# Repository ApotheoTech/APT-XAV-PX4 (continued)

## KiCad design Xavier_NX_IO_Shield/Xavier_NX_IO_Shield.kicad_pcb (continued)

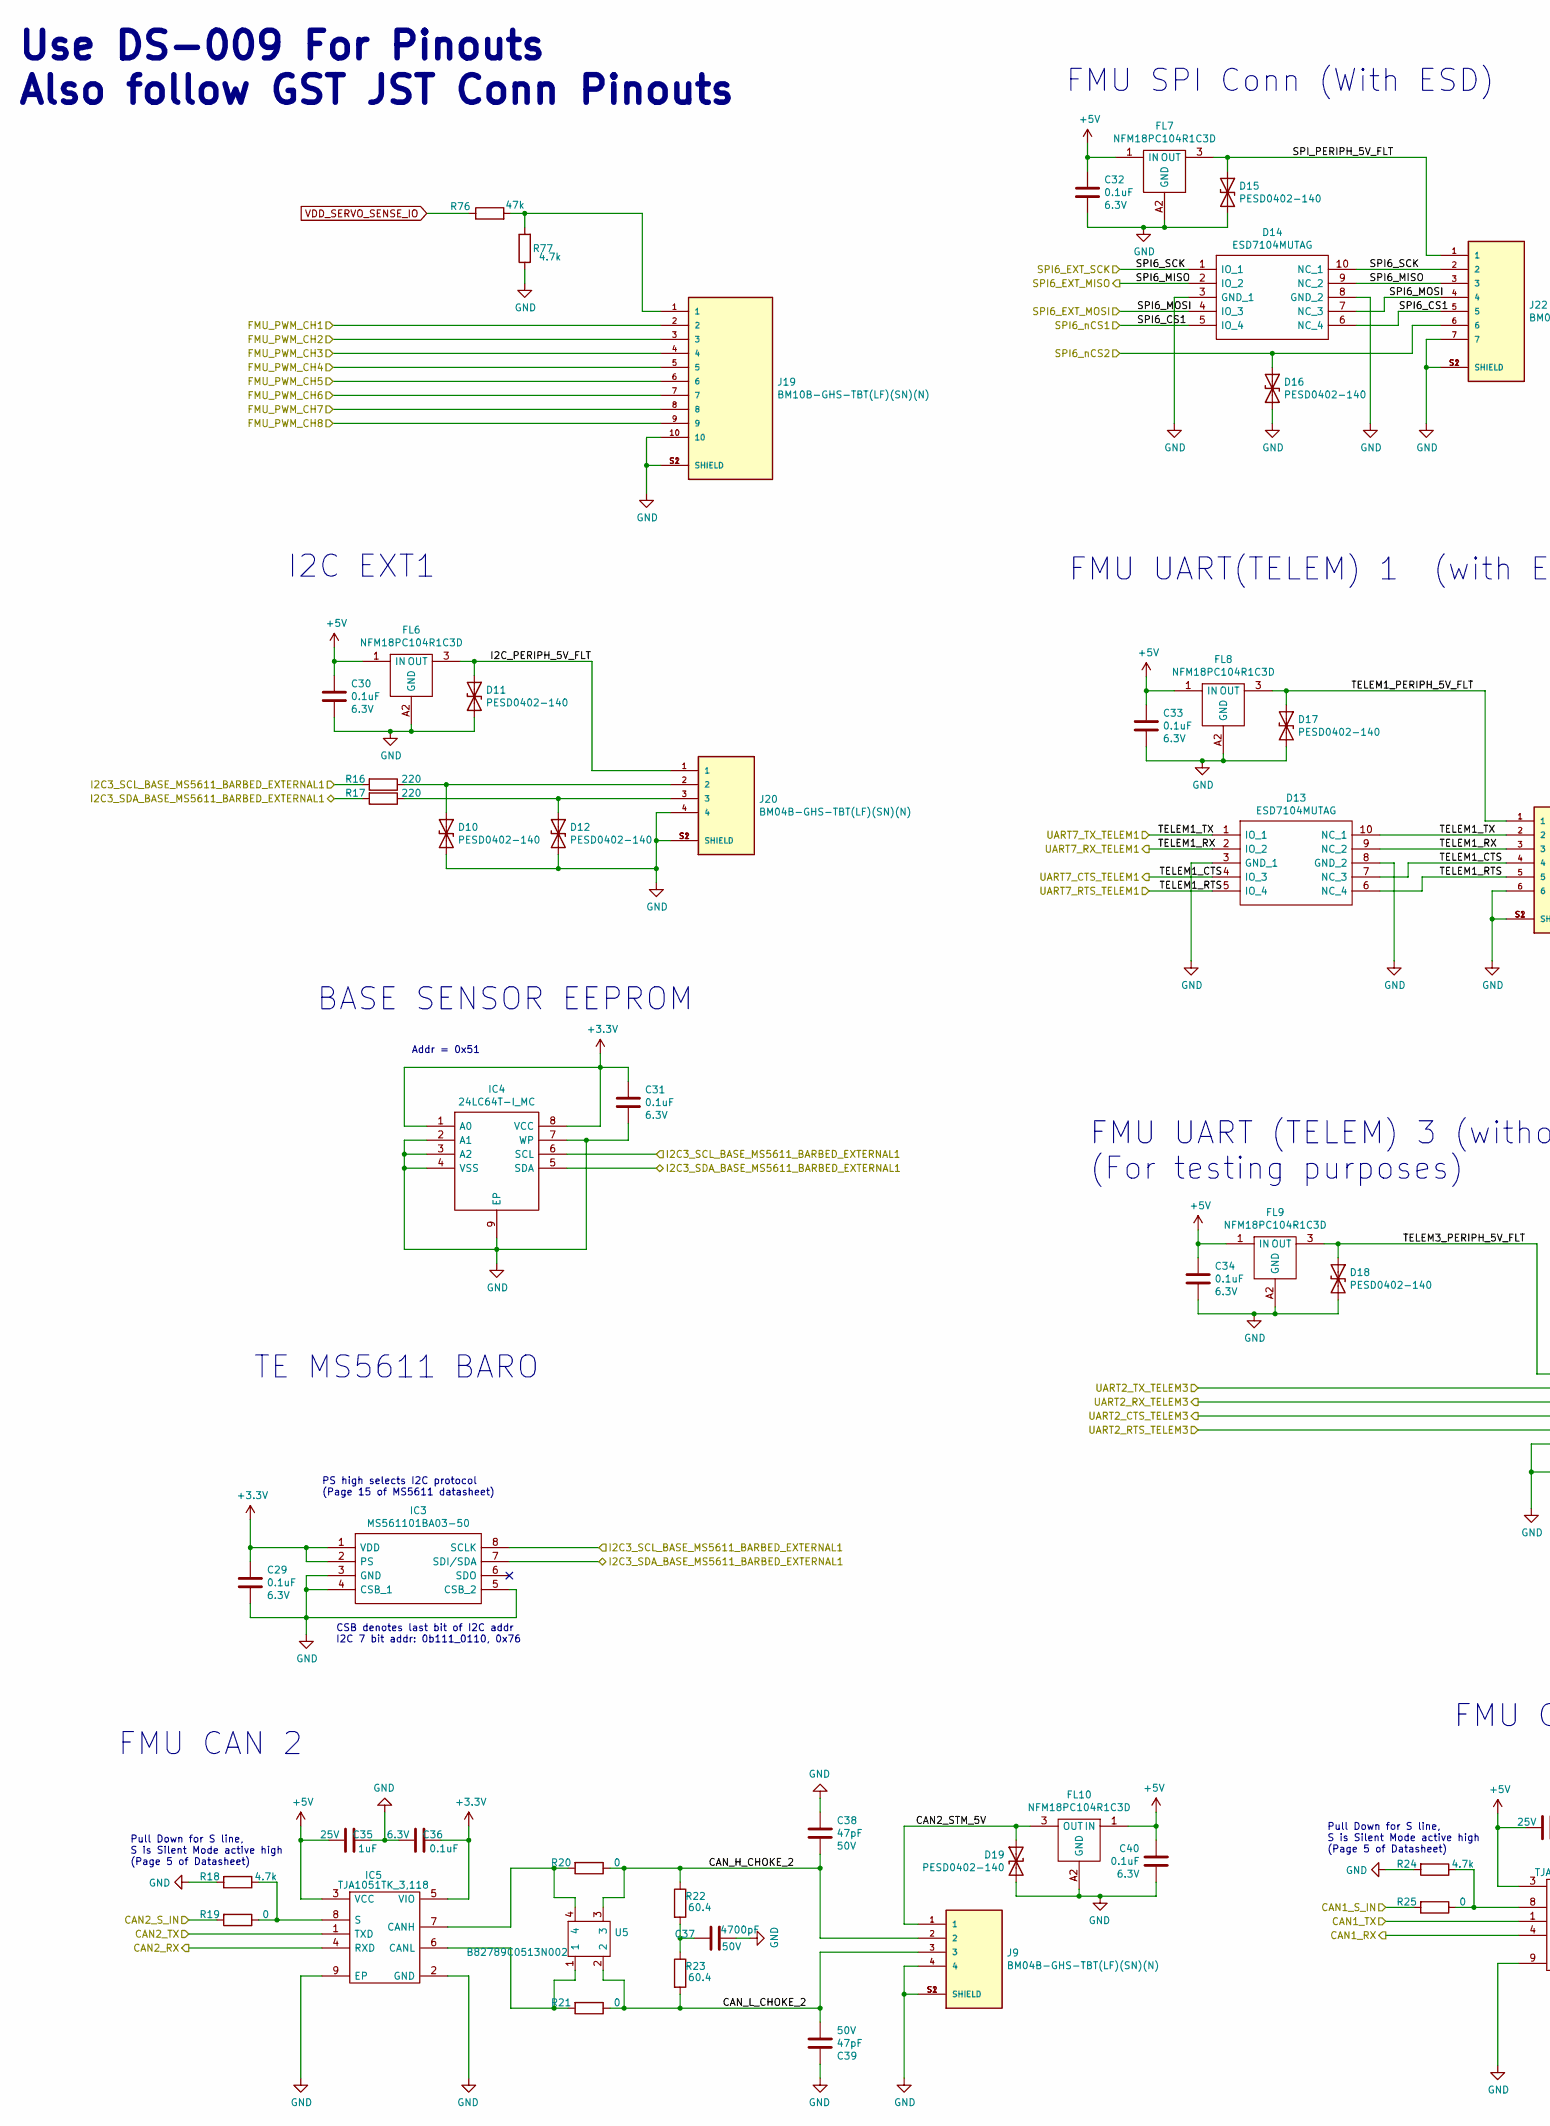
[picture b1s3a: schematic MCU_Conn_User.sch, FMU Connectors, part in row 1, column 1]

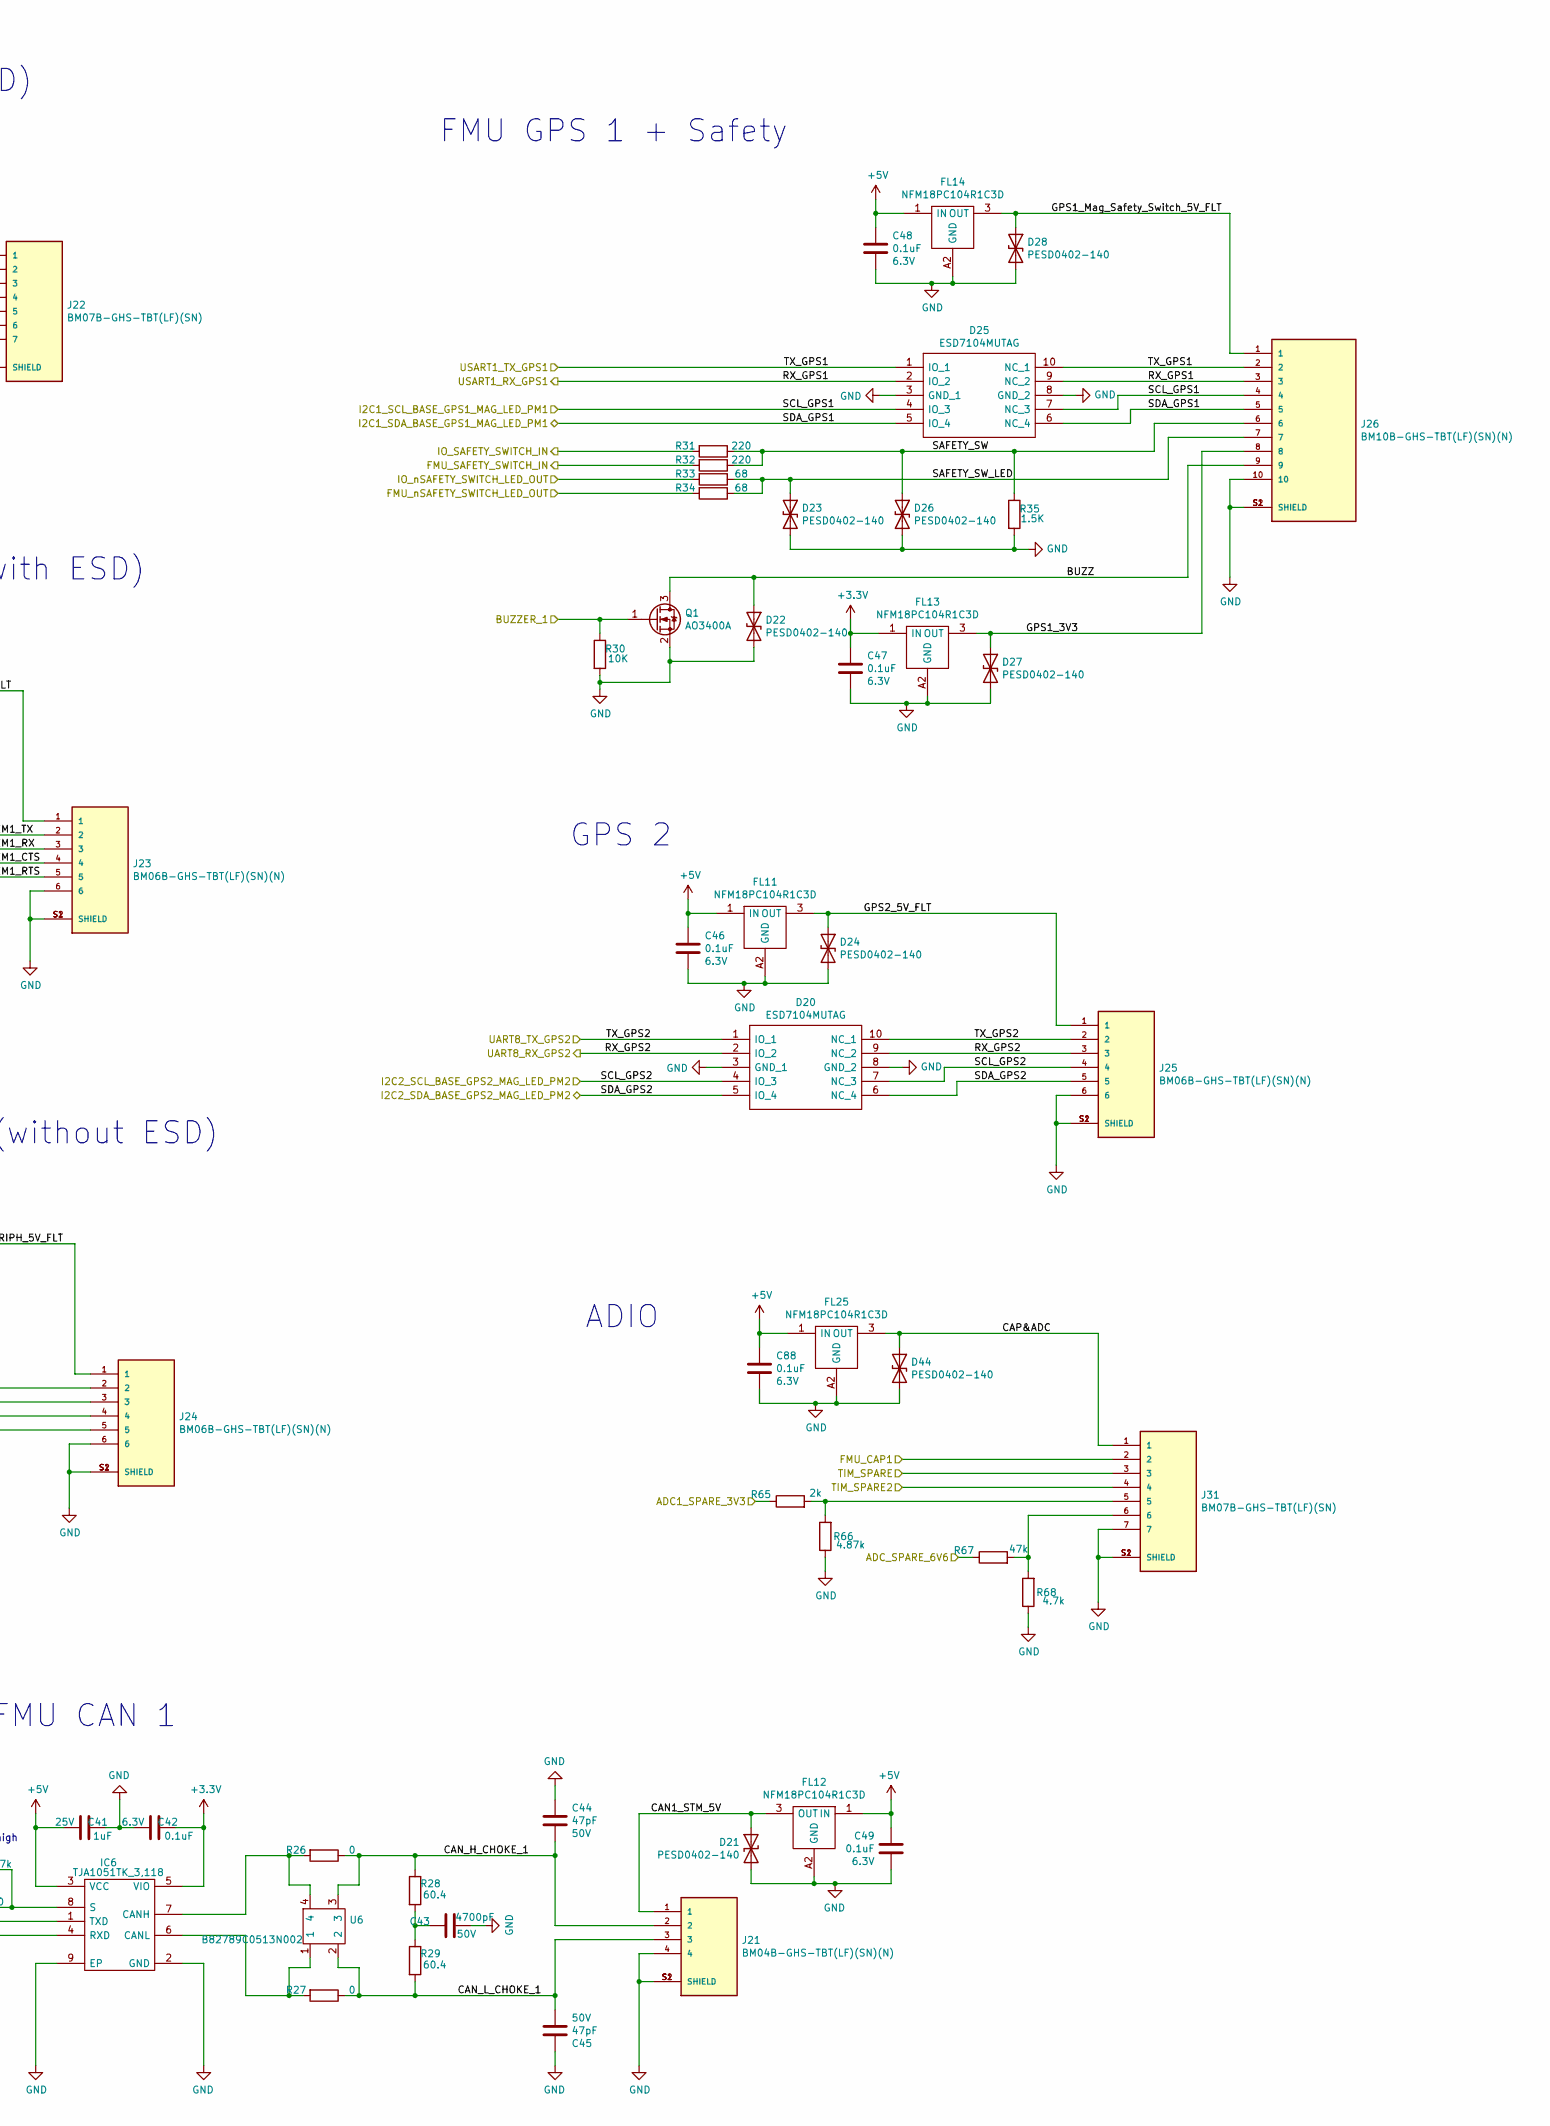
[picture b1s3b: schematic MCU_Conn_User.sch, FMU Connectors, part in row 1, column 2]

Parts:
C29, C30, C31, C32, C33, C34, C36, C40, C42, C46, C47, C48, C49, C88: 0.1uF; C_0402_1005Metric; Voltage 6.3V; PartNumber C1005X5R0J104K050BA
C35, C41: 1uF; C_0402_1005Metric; Voltage 25V; PartNumber GRT155R61E105KE01D
C37, C43: 4700pF; C_0402_1005Metric; Voltage 50V; PartNumber 0402B472J500CT
C38, C39, C44, C45: 47pF; C_0402_1005Metric; Voltage 50V; PartNumber C0402C470J5GACTU
D10, D11, D12, D15, D16, D17, D18, D19, D21, D22, D23, D24, D26, D27, D28, D44: PESD0402-140; PESD0402
D13, D14, D20, D25: ESD7104MUTAG; ESD8104MUTAG; Mouser Part Number 863-ESD7104MUTAG
FL6, FL7, FL8, FL9, FL10, FL11, FL12, FL13, FL14, FL25: NFM18PC104R1C3D; Manufacturer_Part_Number NFM18PC104R1C3D
IC3: MS561101BA03-50; Mouser Part Number 824-MS561101BA03-50
IC4: 24LC64T-I_MC; 24LC64T; Mouser Part Number 579-24LC64T-I/MC
IC5, IC6: TJA1051TK_3,118; TJA1051TK3; Mouser Part Number 771-TJA1051TK/3118
J9, J20, J21: BM04B-GHS-TBT(LF)(SN)(N); PARTREV N/A
J19, J26: BM10B-GHS-TBT(LF)(SN)(N); PARTREV N/A
J22, J31: BM07B-GHS-TBT(LF)(SN); PARTREV NA
J23, J24, J25: BM06B-GHS-TBT(LF)(SN)(N); PARTREV N/A
Q1: AO3400A; SOT-23
R16, R17, R31, R32: 220; R_0402_1005Metric; PartNumber RC0402JR-07220RL
R18, R24: 4.7k; R_0402_1005Metric; PartNumber RC0402FR-074K7L
R19, R20, R21, R25, R26, R27: 0; R_0402_1005Metric; PartNumber CRCW04020000Z0EDHP
R22, R23, R28, R29: 60.4; R_0402_1005Metric; PartNumber ERJ-2RKF60R4X‎
R30: 10K; R_0402_1005Metric; PartNumber ERJ-2RKF1002X
R33, R34: 68; R_0402_1005Metric; PartNumber ‎ERJ-2RKF68R0X‎
R35: 1.5K; R_0402_1005Metric; PartNumber ERJ-2RKF1501X
R65: 2k; R_0402_1005Metric; PartNumber CRCW04022K00FKED
R66: 4.87k; R_0402_1005Metric; PartNumber ERJ-2RKF4871X
R67, R76: 47k; R_0402_1005Metric; PartNumber RCC040247K0FKED
R68, R77: 4.7k; R_0402_1005Metric; PartNumber RCC04024K70FKED
U5, U6: B82789C0513N002; B82789C0113N002

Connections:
+3V3: C29.1, C31.1, C36.2, C42.2, C47.1, FL13.1 (IN), IC3.1 (VDD), IC3.2 (PS), IC4.1 (A0), IC4.8 (VCC), IC5.5 (VIO), IC6.5 (VIO); also elsewhere on the board
+5V: C30.1, C32.1, C33.1, C34.1, C35.1, C40.1, C41.1, C46.1, C48.1, C49.1, C88.1, FL6.1 (IN), FL7.1 (IN), FL8.1 (IN), FL9.1 (IN), FL10.1 (IN), FL11.1 (IN), FL12.1 (IN), FL14.1 (IN), FL25.1 (IN), IC5.3 (VCC), IC6.3 (VCC); also elsewhere on the board
/ADC3_3V3: R65.1; also elsewhere on the board
/ADC3_6V6: R67.1; also elsewhere on the board
/BUZZER1: Q1.1 (G), R30.1; also elsewhere on the board
/CAN1_RX: IC6.4 (RXD); also elsewhere on the board
/CAN1_TX: IC6.1 (TXD); also elsewhere on the board
/CAN2_RX: IC5.4 (RXD); also elsewhere on the board
/CAN2_TX: IC5.1 (TXD); also elsewhere on the board
/FMU_CAP1: J31.2; also elsewhere on the board
/FMU_CH1: J19.2; also elsewhere on the board
/FMU_CH2: J19.3; also elsewhere on the board
/FMU_CH3: J19.4; also elsewhere on the board
/FMU_CH4: J19.5; also elsewhere on the board
/FMU_CH5: J19.6; also elsewhere on the board
/FMU_CH6: J19.7; also elsewhere on the board
/FMU_CH7: J19.8; also elsewhere on the board
/FMU_CH8: J19.9; also elsewhere on the board
/FMU_SAFETY_SWITCH_IN: R32.2; also elsewhere on the board
/FMU_nSAFETY_SWITCH_LED_OUT: R34.2; also elsewhere on the board
/I2C1_SCL_BASE_GPS1_MAG_LED_PM1: D25.4 (IO_3), D25.7 (NC_3), J26.4; also elsewhere on the board
/I2C1_SDA_BASE_GPS1_MAG_LED_PM1: D25.5 (IO_4), D25.6 (NC_4), J26.5; also elsewhere on the board
/I2C2_SCL_BASE_GPS2_MAG_LED_PM2: D20.4 (IO_3), D20.7 (NC_3), J25.4; also elsewhere on the board
/I2C2_SDA_BASE_GPS2_MAG_LED_PM2: D20.5 (IO_4), D20.6 (NC_4), J25.5; also elsewhere on the board
/I2C3_SCL_BASE_MS5611_BARBED_EXTERNAL: IC3.8 (SCLK), IC4.6 (SCL), R16.2; also elsewhere on the board
/I2C3_SDA_BASE_MS5611_BARBED_EXTERNAL: IC3.7 (SDI/SDA), IC4.5 (SDA), R17.2; also elsewhere on the board
/IO_SAFETY_SWITCH_IN: R31.2; also elsewhere on the board
/IO_nSAFETY_SWITCH_LED_OUT: R33.2; also elsewhere on the board
/MCU_Conn_User/BUZZ: D22.1 (A1), J26.9, Q1.3 (D)
/MCU_Conn_User/CAN1_STM_5V: D21.1 (A1), FL12.3 (OUT), J21.1
/MCU_Conn_User/CAN2_STM_5V: D19.1 (A1), FL10.3 (OUT), J9.1
/MCU_Conn_User/CAN_H_CHOKE_1: C44.2, J21.2, R26.1, R28.1, U6.3
/MCU_Conn_User/CAN_H_CHOKE_2: C38.2, J9.2, R20.1, R22.1, U5.3
/MCU_Conn_User/CAN_L_CHOKE_1: C45.2, J21.3, R27.1, R29.2, U6.2
/MCU_Conn_User/CAN_L_CHOKE_2: C39.2, J9.3, R21.1, R23.2, U5.2
/MCU_Conn_User/CAP&ADC: D44.1 (A1), FL25.3 (OUT), J31.1
/MCU_Conn_User/GPS1_3V3: D27.1 (A1), FL13.3 (OUT), J26.8
/MCU_Conn_User/GPS1_Mag_Safety_Switch_5V_FLT: D28.1 (A1), FL14.3 (OUT), J26.1
/MCU_Conn_User/GPS2_5V_FLT: D24.1 (A1), FL11.3 (OUT), J25.1
/MCU_Conn_User/I2C_PERIPH_5V_FLT: D11.1 (A1), FL6.3 (OUT), J20.1
/MCU_Conn_User/SAFETY_SW: D26.1 (A1), J26.6, R31.1, R32.1, R35.1
/MCU_Conn_User/SAFETY_SW_LED: D23.1 (A1), J26.7, R33.1, R34.1
/MCU_Conn_User/SPI_PERIPH_5V_FLT: D15.1 (A1), FL7.3 (OUT), J22.1
/MCU_Conn_User/TELEM1_PERIPH_5V_FLT: D17.1 (A1), FL8.3 (OUT), J23.1
/MCU_Conn_User/TELEM3_PERIPH_5V_FLT: D18.1 (A1), FL9.3 (OUT), J24.1
/SPI6_DRDY2_EXTERNAL1: J31.3; also elsewhere on the board
/SPI6_MISO_EXTERNAL1: D14.2 (IO_2), D14.9 (NC_2), J22.3; also elsewhere on the board
/SPI6_MOSI_EXTERNAL1: D14.4 (IO_3), D14.7 (NC_3), J22.4; also elsewhere on the board
/SPI6_SCK_EXTERAL1: D14.1 (IO_1), D14.10 (NC_1), J22.2; also elsewhere on the board
/SPI6_nCS1_EXTERNAL1: D14.5 (IO_4), D14.6 (NC_4), J22.5; also elsewhere on the board
/SPI6_nCS2_EXTERNAL1: D16.1 (A1), J22.6; also elsewhere on the board
/SPIX_SYNC: J31.4; also elsewhere on the board
/UART7_CTS_TELEM1: D13.4 (IO_3), D13.7 (NC_3), J23.4; also elsewhere on the board
/UART7_RTS_TELEM1: D13.5 (IO_4), D13.6 (NC_4), J23.5; also elsewhere on the board
/UART7_RX_TELEM1: D13.2 (IO_2), D13.9 (NC_2), J23.3; also elsewhere on the board
/UART7_TX_TELEM1: D13.1 (IO_1), D13.10 (NC_1), J23.2; also elsewhere on the board
/UART8_RX_GPS2: D20.2 (IO_2), D20.9 (NC_2), J25.3; also elsewhere on the board
/UART8_TX_GPS2: D20.1 (IO_1), D20.10 (NC_1), J25.2; also elsewhere on the board
/USART1_RX_GPS1: D25.2 (IO_2), D25.9 (NC_2), J26.3; also elsewhere on the board
/USART1_TX_GPS1: D25.1 (IO_1), D25.10 (NC_1), J26.2; also elsewhere on the board
/USART2_CTS_TELEM3: J24.4; also elsewhere on the board
/USART2_RTS_TELEM3: J24.5; also elsewhere on the board
/USART2_RX_TELEM3: J24.3; also elsewhere on the board
/USART2_TX_TELEM3: J24.2; also elsewhere on the board
/nPOWER_IN_B: R19.2; also elsewhere on the board
/nPOWER_IN_C: R25.2; also elsewhere on the board
GND: C29.2, C30.2, C31.2, C32.2, C33.2, C34.2, C35.2, C36.1, C37.2, C38.1, C39.1, C40.2, C41.2, C42.1, C43.2, C44.1, C45.1, C46.2, C47.2, C48.2, C49.2, C88.2, D10.2 (A2), D11.2 (A2), D12.2 (A2), D13.3 (GND_1), D13.8 (GND_2), D14.3 (GND_1), D14.8 (GND_2), D15.2 (A2), D16.2 (A2), D17.2 (A2), D18.2 (A2), D19.2 (A2), D20.3 (GND_1), D20.8 (GND_2), D21.2 (A2), D22.2 (A2), D23.2 (A2), D24.2 (A2), D25.3 (GND_1), D25.8 (GND_2), D26.2 (A2), D27.2 (A2), D28.2 (A2), D44.2 (A2), FL6.A2 (GND), FL7.A2 (GND), FL8.A2 (GND), FL9.A2 (GND), FL10.A2 (GND), FL11.A2 (GND), FL12.A2 (GND), FL13.A2 (GND), FL14.A2 (GND), FL25.A2 (GND), IC3.3 (GND), IC3.4 (CSB_1), IC3.5 (CSB_2), IC4.2 (A1), IC4.3 (A2), IC4.4 (VSS), IC4.7 (WP), IC4.9 (EP), IC5.2 (GND), IC5.9 (EP), IC6.2 (GND), IC6.9 (EP), J9.4, J9.S1 (SHIELD), J9.S2 (SHIELD), J19.10, J19.S1 (SHIELD), J19.S2 (SHIELD), J20.4, J20.S1 (SHIELD), J20.S2 (SHIELD), J21.4, J21.S1 (SHIELD), J21.S2 (SHIELD), J22.7, J22.S1 (SHIELD), J22.S2 (SHIELD), J23.6, J23.S1 (SHIELD), J23.S2 (SHIELD), J24.6, J24.S1 (SHIELD), J24.S2 (SHIELD), J25.6, J25.S1 (SHIELD), J25.S2 (SHIELD), J26.10, J26.S1 (SHIELD), J26.S2 (SHIELD), J31.7, J31.S1 (SHIELD), J31.S2 (SHIELD), Q1.2 (S), R18.2, R24.2, R30.2, R35.2, R66.1, R68.1, R77.1; also elsewhere on the board
unnamed: C37.1, R22.2, R23.1
unnamed: C43.1, R28.2, R29.1
unnamed: D10.1 (A1), J20.2, R16.1
unnamed: D12.1 (A1), J20.3, R17.1
unnamed: IC5.6 (CANL), R21.2, U5.1
unnamed: IC5.7 (CANH), R20.2, U5.4
unnamed: IC5.8 (S), R18.1, R19.1
unnamed: IC6.6 (CANL), R27.2, U6.1
unnamed: IC6.7 (CANH), R26.2, U6.4
unnamed: IC6.8 (S), R24.1, R25.1
unnamed: J19.1, R76.2, R77.2
unnamed: J31.5, R65.2, R66.2
unnamed: J31.6, R67.2, R68.2
VDD_SERVO_SENSE_IO: R76.1; also elsewhere on the board

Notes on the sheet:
I2C EXT1
BASE SENSOR EEPROM
Addr = 0x51
TE MS5611 BARO
FMU SPI Conn (With ESD)
FMU UART(TELEM) 1 (with ESD)
FMU UART (TELEM) 3 (without ESD) (For testing purposes)
FMU CAN 1
FMU CAN 2
FMU GPS 1 + Safety
GPS 2
ADIO
CSB denotes last bit of I2C addr I2C 7 bit addr: 0b111_0110, 0x76
PS high selects I2C protocol (Page 15 of MS5611 datasheet)
Use DS-009 For Pinouts Also follow GST JST Conn Pinouts
Pull Down for S line, S is Silent Mode active high (Page 5 of Datasheet)

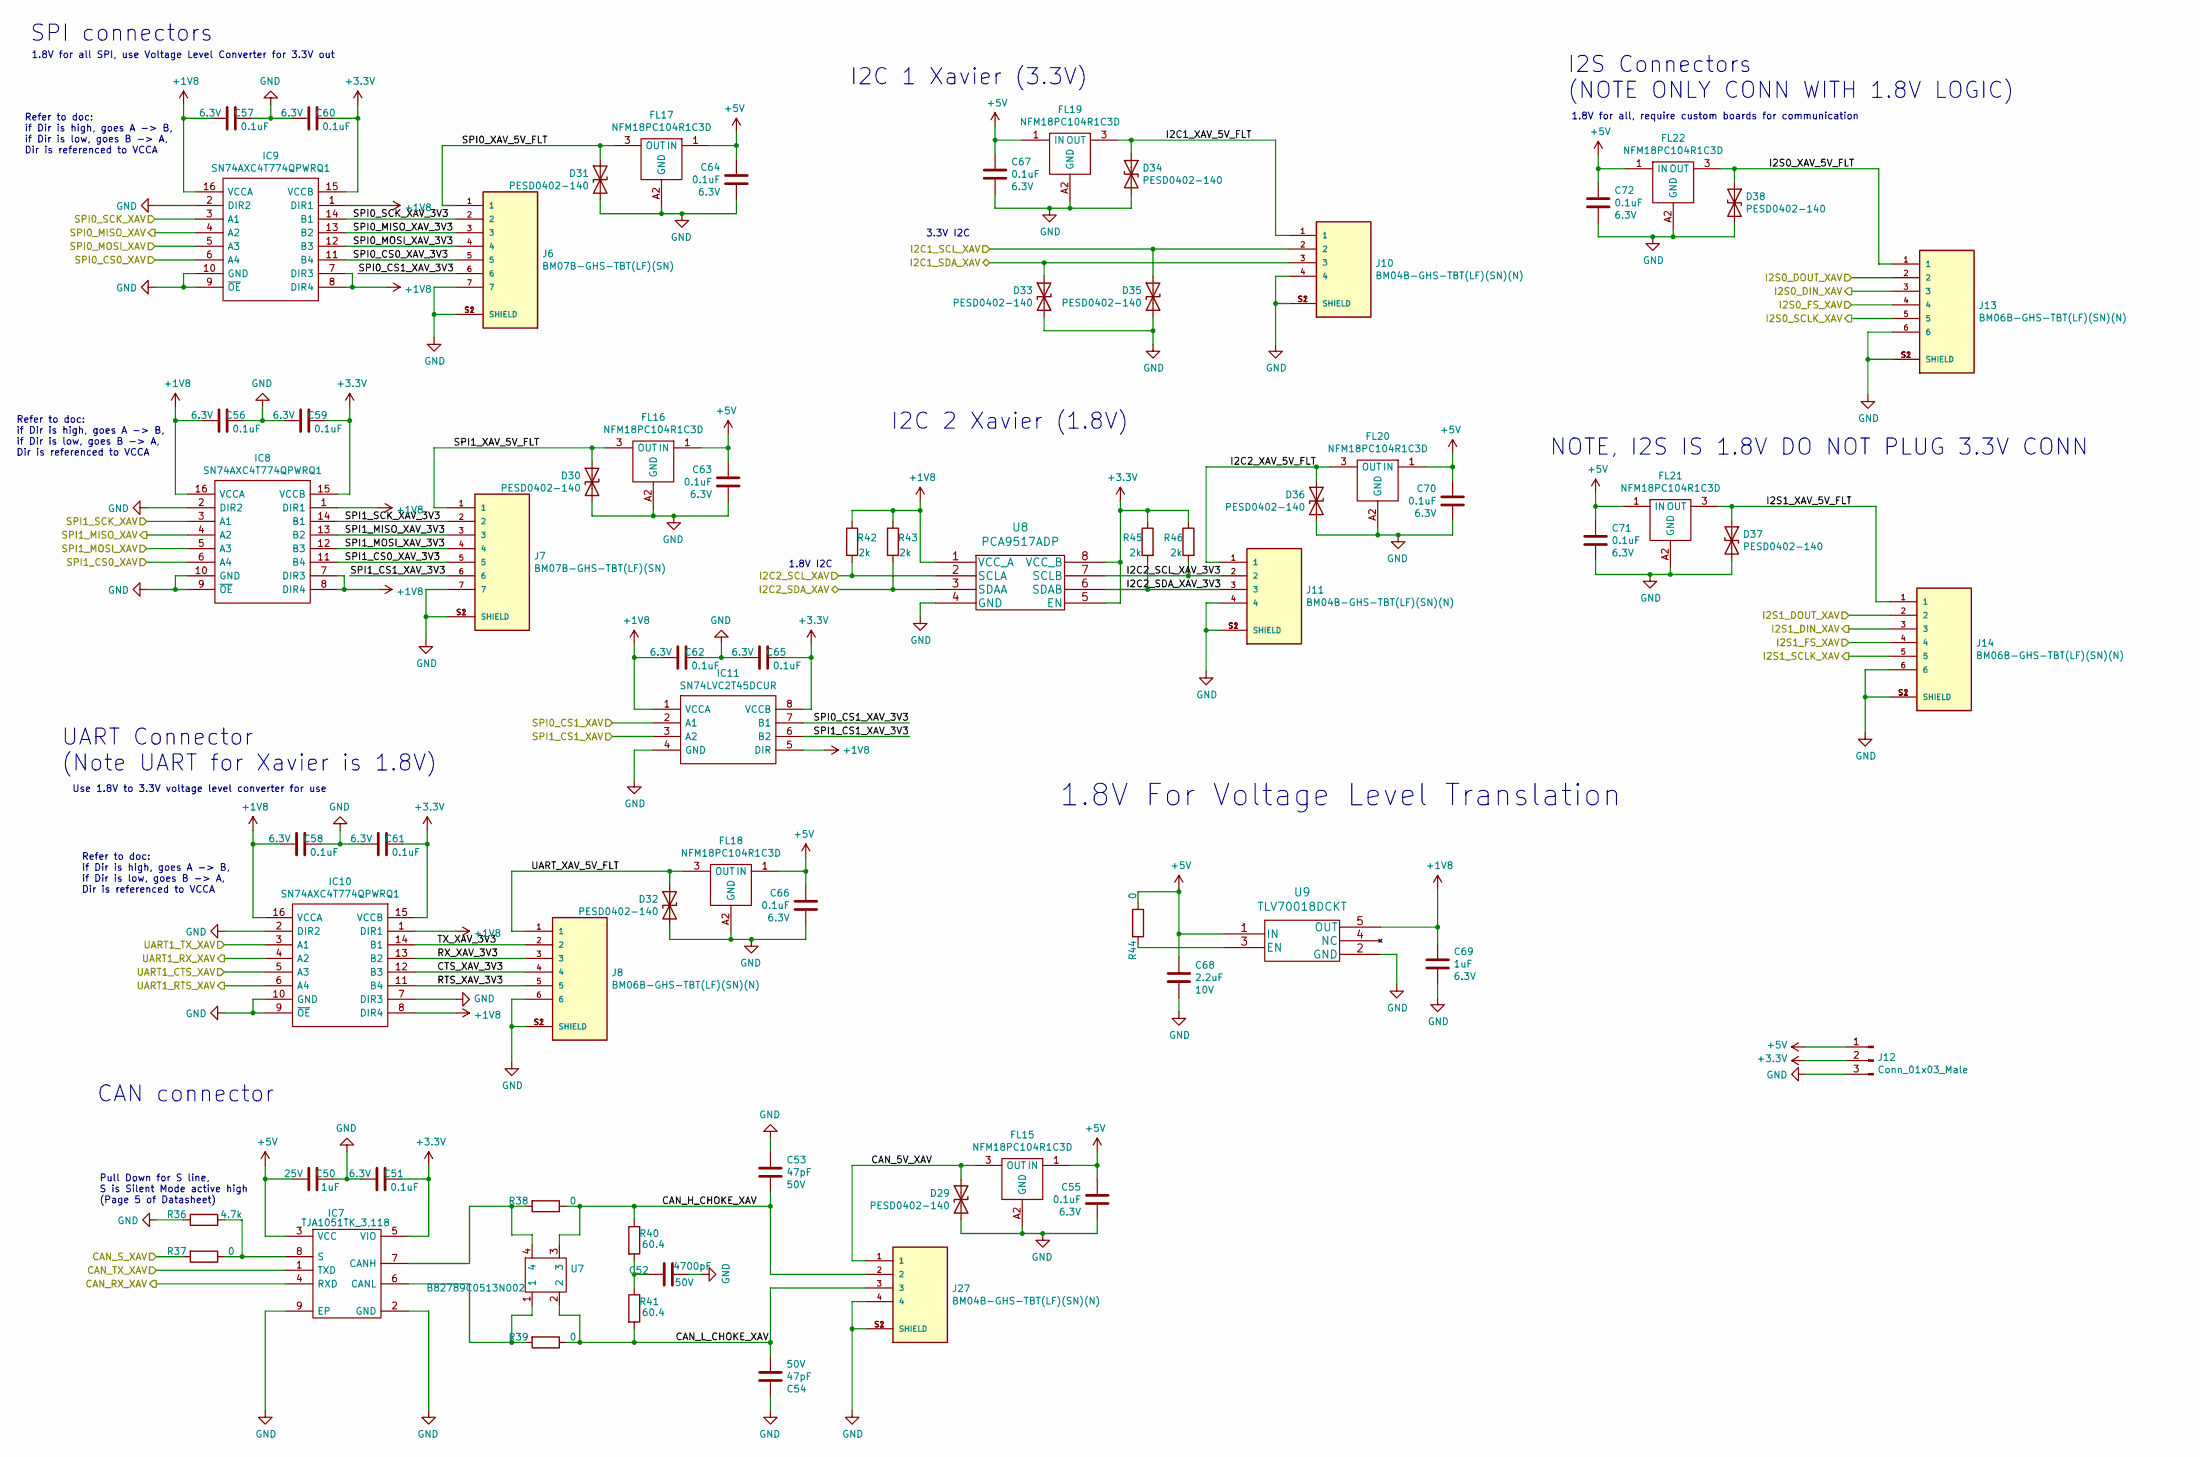
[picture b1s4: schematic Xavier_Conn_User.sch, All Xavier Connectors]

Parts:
C50: 1uF; C_0402_1005Metric; Voltage 25V; PartNumber GRT155R61E105KE01D
C51, C55, C56, C57, C58, C59, C60, C61, C62, C63, C64, C65, C66, C67, C70, C71, C72: 0.1uF; C_0402_1005Metric; Voltage 6.3V; PartNumber C1005X5R0J104K050BA
C52: 4700pF; C_0402_1005Metric; Voltage 50V; PartNumber 0402B472J500CT
C53, C54: 47pF; C_0402_1005Metric; Voltage 50V; PartNumber C0402C470J5GACTU
C68: 2.2uF; C_0402_1005Metric; Voltage 10V; PartNumber C1005X5R1A225K050BC
C69: 1uF; C_0402_1005Metric; Voltage 6.3V; PartNumber C0402C105Z9VACTU
D29, D30, D31, D32, D33, D34, D35, D36, D37, D38: PESD0402-140; PESD0402
FL15, FL16, FL17, FL18, FL19, FL20, FL21, FL22: NFM18PC104R1C3D; Manufacturer_Part_Number NFM18PC104R1C3D
IC7: TJA1051TK_3,118; TJA1051TK3; Mouser Part Number 771-TJA1051TK/3118
IC8, IC9, IC10: SN74AXC4T774QPWRQ1; Mouser Part Number 595-74AXC4T774QPWRQ1
IC11: SN74LVC2T45DCUR; Mouser Part Number 595-SN74LVC2T45DCUR
J6, J7: BM07B-GHS-TBT(LF)(SN); PARTREV NA
J8, J13, J14: BM06B-GHS-TBT(LF)(SN)(N); PARTREV N/A
J10, J11, J27: BM04B-GHS-TBT(LF)(SN)(N); PARTREV N/A
J12: Conn_01x03_Male; PinHeader_1x03_P2.54mm_Vertical
R36: 4.7k; R_0402_1005Metric; PartNumber RC0402FR-074K7L
R37, R38, R39, R44: 0; R_0402_1005Metric; PartNumber CRCW04020000Z0EDHP
R40, R41: 60.4; R_0402_1005Metric; PartNumber ERJ-2RKF60R4X‎
R42, R43, R45, R46: 2k; R_0402_1005Metric; PartNumber CRCW04022K00FKED
U7: B82789C0513N002; B82789C0113N002
U8: PCA9517ADP
U9: TLV70018DCKT

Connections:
+1V8: C56.1, C57.1, C58.1, C62.1, C69.1, IC8.1 (DIR1), IC8.7 (DIR3), IC8.8 (DIR4), IC8.16 (VCCA), IC9.1 (DIR1), IC9.7 (DIR3), IC9.8 (DIR4), IC9.16 (VCCA), IC10.1 (DIR1), IC10.8 (DIR4), IC10.16 (VCCA), IC11.1 (VCCA), IC11.5 (DIR), R42.1, R43.1, U8.1 (VCC_A), U9.5 (OUT)
+3V3: C51.2, C59.2, C60.2, C61.2, C65.2, IC7.5 (VIO), IC8.15 (VCCB), IC9.15 (VCCB), IC10.15 (VCCB), IC11.8 (VCCB), J12.2, R45.1, R46.1, U8.5 (EN), U8.8 (VCC_B); also elsewhere on the board
+5V: C50.1, C55.1, C63.1, C64.1, C66.1, C67.1, C68.1, C70.1, C71.1, C72.1, FL15.1 (IN), FL16.1 (IN), FL17.1 (IN), FL18.1 (IN), FL19.1 (IN), FL20.1 (IN), FL21.1 (IN), FL22.1 (IN), IC7.3 (VCC), J12.1, R44.1, U9.1 (IN); also elsewhere on the board
/CAN_RX_XAV: IC7.4 (RXD); also elsewhere on the board
/CAN_TX_XAV: IC7.1 (TXD); also elsewhere on the board
/I2C1_SCL_XAV: D35.1 (A1), J10.2; also elsewhere on the board
/I2C1_SDA_XAV: D33.1 (A1), J10.3; also elsewhere on the board
/I2C2_SCL_XAV: R42.2, U8.2 (SCLA); also elsewhere on the board
/I2C2_SDA_XAV: R43.2, U8.3 (SDAA); also elsewhere on the board
/I2S0_DIN_XAV: J13.3; also elsewhere on the board
/I2S0_DOUT_XAV: J13.2; also elsewhere on the board
/I2S0_FS_XAV: J13.4; also elsewhere on the board
/I2S0_SCLK_XAV: J13.5; also elsewhere on the board
/I2S1_DIN_XAV: J14.3; also elsewhere on the board
/I2S1_DOUT_XAV: J14.2; also elsewhere on the board
/I2S1_FS_XAV: J14.4; also elsewhere on the board
/I2S1_SCLK_XAV: J14.5; also elsewhere on the board
/SD_DAT0_XAV: R37.2; also elsewhere on the board
/SPI0_CS0_XAV: IC9.6 (A4); also elsewhere on the board
/SPI0_CS1_XAV: IC11.2 (A1); also elsewhere on the board
/SPI0_MISO_XAV: IC9.4 (A2); also elsewhere on the board
/SPI0_MOSI_XAV: IC9.5 (A3); also elsewhere on the board
/SPI0_SCK_XAV: IC9.3 (A1); also elsewhere on the board
/SPI1_CS0_XAV: IC8.6 (A4); also elsewhere on the board
/SPI1_CS1_XAV: IC11.3 (A2); also elsewhere on the board
/SPI1_MISO_XAV: IC8.4 (A2); also elsewhere on the board
/SPI1_MOSI_XAV: IC8.5 (A3); also elsewhere on the board
/SPI1_SCK_XAV: IC8.3 (A1); also elsewhere on the board
/UART1_CTS_XAV: IC10.5 (A3); also elsewhere on the board
/UART1_RTS_XAV: IC10.6 (A4); also elsewhere on the board
/UART1_RXD_XAV: IC10.4 (A2); also elsewhere on the board
/UART1_TXD_XAV: IC10.3 (A1); also elsewhere on the board
/Xavier_Conn_User/CAN_5V_XAV: D29.1 (A1), FL15.3 (OUT), J27.1
/Xavier_Conn_User/CAN_H_CHOKE_XAV: C53.2, J27.2, R38.1, R40.1, U7.3
/Xavier_Conn_User/CAN_L_CHOKE_XAV: C54.2, J27.3, R39.1, R41.2, U7.2
/Xavier_Conn_User/CTS_XAV_3V3: IC10.12 (B3), J8.4
/Xavier_Conn_User/I2C1_XAV_5V_FLT: D34.1 (A1), FL19.3 (OUT), J10.1
/Xavier_Conn_User/I2C2_SCL_XAV_3V3: J11.2, R46.2, U8.7 (SCLB)
/Xavier_Conn_User/I2C2_SDA_XAV_3V3: J11.3, R45.2, U8.6 (SDAB)
/Xavier_Conn_User/I2C2_XAV_5V_FLT: D36.1 (A1), FL20.3 (OUT), J11.1
/Xavier_Conn_User/I2S0_XAV_5V_FLT: D38.1 (A1), FL22.3 (OUT), J13.1
/Xavier_Conn_User/I2S1_XAV_5V_FLT: D37.1 (A1), FL21.3 (OUT), J14.1
/Xavier_Conn_User/RTS_XAV_3V3: IC10.11 (B4), J8.5
/Xavier_Conn_User/RX_XAV_3V3: IC10.13 (B2), J8.3
/Xavier_Conn_User/SPI0_CS0_XAV_3V3: IC9.11 (B4), J6.5
/Xavier_Conn_User/SPI0_CS1_XAV_3V3: IC11.7 (B1), J6.6
/Xavier_Conn_User/SPI0_MISO_XAV_3V3: IC9.13 (B2), J6.3
/Xavier_Conn_User/SPI0_MOSI_XAV_3V3: IC9.12 (B3), J6.4
/Xavier_Conn_User/SPI0_SCK_XAV_3V3: IC9.14 (B1), J6.2
/Xavier_Conn_User/SPI0_XAV_5V_FLT: D31.1 (A1), FL17.3 (OUT), J6.1
/Xavier_Conn_User/SPI1_CS0_XAV_3V3: IC8.11 (B4), J7.5
/Xavier_Conn_User/SPI1_CS1_XAV_3V3: IC11.6 (B2), J7.6
/Xavier_Conn_User/SPI1_MISO_XAV_3V3: IC8.13 (B2), J7.3
/Xavier_Conn_User/SPI1_MOSI_XAV_3V3: IC8.12 (B3), J7.4
/Xavier_Conn_User/SPI1_SCK_XAV_3V3: IC8.14 (B1), J7.2
/Xavier_Conn_User/SPI1_XAV_5V_FLT: D30.1 (A1), FL16.3 (OUT), J7.1
/Xavier_Conn_User/TX_XAV_3V3: IC10.14 (B1), J8.2
/Xavier_Conn_User/UART_XAV_5V_FLT: D32.1 (A1), FL18.3 (OUT), J8.1
GND: C50.2, C51.1, C52.2, C53.1, C54.1, C55.2, C56.2, C57.2, C58.2, C59.1, C60.1, C61.1, C62.2, C63.2, C64.2, C65.1, C66.2, C67.2, C68.2, C69.2, C70.2, C71.2, C72.2, D29.2 (A2), D30.2 (A2), D31.2 (A2), D32.2 (A2), D33.2 (A2), D34.2 (A2), D35.2 (A2), D36.2 (A2), D37.2 (A2), D38.2 (A2), FL15.A2 (GND), FL16.A2 (GND), FL17.A2 (GND), FL18.A2 (GND), FL19.A2 (GND), FL20.A2 (GND), FL21.A2 (GND), FL22.A2 (GND), IC7.2 (GND), IC7.9 (EP), IC8.2 (DIR2), IC8.9 (~OE), IC8.10 (GND), IC9.2 (DIR2), IC9.9 (~OE), IC9.10 (GND), IC10.2 (DIR2), IC10.7 (DIR3), IC10.9 (~OE), IC10.10 (GND), IC11.4 (GND), J6.7, J6.S1 (SHIELD), J6.S2 (SHIELD), J7.7, J7.S1 (SHIELD), J7.S2 (SHIELD), J8.6, J8.S1 (SHIELD), J8.S2 (SHIELD), J10.4, J10.S1 (SHIELD), J10.S2 (SHIELD), J11.4, J11.S1 (SHIELD), J11.S2 (SHIELD), J12.3, J13.6, J13.S1 (SHIELD), J13.S2 (SHIELD), J14.6, J14.S1 (SHIELD), J14.S2 (SHIELD), J27.4, J27.S1 (SHIELD), J27.S2 (SHIELD), R36.2, U8.4 (GND), U9.2 (GND); also elsewhere on the board
unnamed: C52.1, R40.2, R41.1
unnamed: IC7.6 (CANL), R39.2, U7.1
unnamed: IC7.7 (CANH), R38.2, U7.4
unnamed: IC7.8 (S), R36.1, R37.1
unnamed: R44.2, U9.3 (EN)

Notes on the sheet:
SPI connectors
CAN connector
UART Connector (Note UART for Xavier is 1.8V)
I2S Connectors (NOTE ONLY CONN WITH 1.8V LOGIC)
I2C 1 Xavier (3.3V)
3.3V I2C
1.8V for all, require custom boards for communication
1.8V for all SPI, use Voltage Level Converter for 3.3V out
Use 1.8V to 3.3V voltage level converter for use
Pull Down for S line, S is Silent Mode active high (Page 5 of Datasheet)
I2C 2 Xavier (1.8V)
1.8V I2C
Refer to doc: if Dir is high, goes A -> B, if Dir is low, goes B -> A, Dir is referenced to VCCA
1.8V For Voltage Level Translation
NOTE, I2S IS 1.8V DO NOT PLUG 3.3V CONN

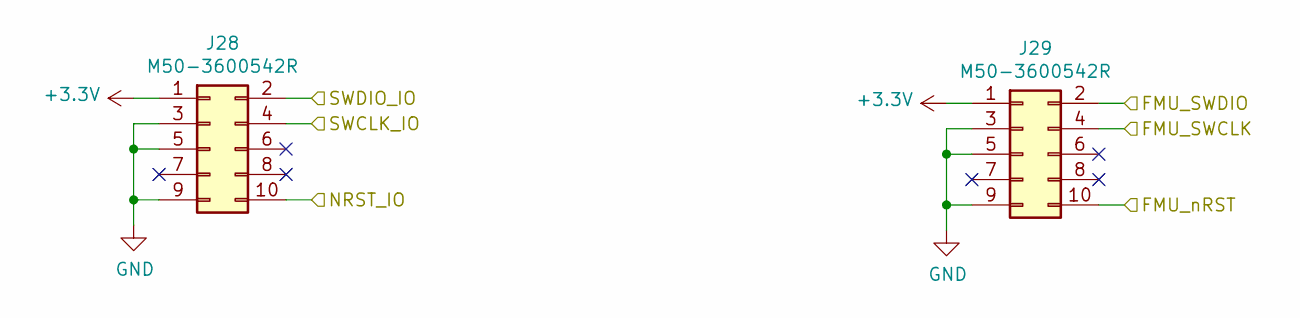
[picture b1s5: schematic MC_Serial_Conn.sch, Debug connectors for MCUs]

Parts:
J28, J29: ‎M50-3600542R‎; M503600542

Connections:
+3V3: J28.1, J29.1; also elsewhere on the board
/Debug Serial Connectors/SWCLK_IO: J28.4; also elsewhere on the board
/Debug Serial Connectors/SWDIO_IO: J28.2; also elsewhere on the board
/FMU_SWCLK: J29.4; also elsewhere on the board
/FMU_SWDIO: J29.2; also elsewhere on the board
/FMU_nRST: J29.10; also elsewhere on the board
GND: J28.3, J28.5, J28.9, J29.3, J29.5, J29.9; also elsewhere on the board
NRST_IO: J28.10; also elsewhere on the board
